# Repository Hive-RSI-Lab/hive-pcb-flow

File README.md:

# hive-pcb-flow

The pcb-flow module: KiCad hardware design for the Hive, in the Hive org like the other modules. It began as ihsan-sa/pcb-flow's Claude Code skill and is its own now ([where it came from](docs/upstream.md)).

An agent designs a PCB from a written brief: research, architecture, parts, schematic, placement, routing, then the checks (ERC, DRC, the verify suite, JLCPCB DFM on the exported Gerbers), ending in a fab package. The person signs off between stages. Ordering and paying are always the person's.

- [`docs/README.md`](docs/README.md): how an agent uses it in the Hive; [`docs/playbook.md`](docs/playbook.md): the phases, gates and fix loop
- `agents/`: the role prompts the playbook spawns; `scripts/`: the checks and tools; `reference/`: their tables, recipes, checklists and knowledge records
- [`docs/tools.md`](docs/tools.md): every tool pcb-flow uses, with licences and how to install it
- `tests/`: unit tests for the scripts (`test_env_lookups.py`: the lookups for the Hive's shared tools folder), and `tests/workarounds/`, the probes
- `bin/pcb-flow`: runs the scripts in a Hive sandbox with the Hive's KiCad 10 and freerouting (`pcb-flow check` first)
- The first board made with it: [boards/hwde-led-test/](boards/hwde-led-test/)
- [docs/errata-corpus.md](docs/errata-corpus.md): public boards whose rev B fixed a rev A defect, and which of those defects pcb-flow's checks catch on rev A (`bin/pcb-flow errata_corpus fetch|run|table`)
- [docs/miss-taxonomy.md](docs/miss-taxonomy.md): the corpus misses grouped by the check that would see them, ranked by count times how much of a board the check judges
- [docs/research/](docs/research/README.md): current research turned into checks: `bin/pcb-flow papers` scans the topics in `reference/research/watch.yaml`, reads legitimate open copies (the rest go on [the person's list](docs/research/paywalled.md)), and gives each claim pcb-flow's own verdict, with the test that reached it; only reproduced claims become [guidelines](docs/research/guidelines.md)
- [docs/route-quality.md](docs/route-quality.md): a layout judged as good, not only legal: `route_quality` scores each net class against its shortest 45-degree routes, `route_improve` re-routes the worst nets in rounds and stops when a round stops gaining
- `bin/pcb-flow part_repair`: move, rotate or re-pad parts on a routed board (place_edit's `swap_fp` puts a fixed library footprint in, `renumber` gives pads new numbers): it rips the copper the change spoils in a window round each part, makes the change, routes every net back to as few islands as it had, and keeps the result only if no net has more islands, DRC is no worse and no violation is new near the repair; it writes the op files that replay it (rip, place, route) and a REPORT.md

## Tools and credits

pcb-flow stands on other people's open-source tools: [KiCad](https://www.kicad.org/) for everything board-shaped, [KiCadRoutingTools](https://github.com/drandyhaas/KiCadRoutingTools) by Andy Haas (MIT) for escape and critical routing, [Freerouting](https://github.com/freerouting/freerouting) for bulk routing, [easyeda2kicad](https://github.com/uPesy/easyeda2kicad.py) for LCSC parts, and ngspice, Xyce, openEMS, Palace, gmsh, FastHenry2 and FasterCap (from the IIC-OSIC-TOOLS image) for simulation. [docs/tools.md](docs/tools.md) lists every tool with its version, licence, what it is for and how a fresh Hive gets it; `bin/pcb-flow check` shows what a machine has. [NOTICE](NOTICE) says what the MIT licence does not cover.

## Test and score

- **Test**, `bin/pcb-flow test`, run on every change: upstream's unit tests
  for the skill's scripts (in `tests/`, from ihsan-sa/pcb-flow, about 2,400 of
  them) and the workaround probes. It leaves out tests marked `smoke` (a
  live KiCad run) or `net` (the internet), and points `HWDE_BOARDS_ROOT` at
  an empty dir, so tests that want a real board skip. Upstream tests that
  fail here for a cause a brief already owns are expected failures, listed
  with that brief in `tests/conftest.py`; one that starts passing shows as
  XPASS, and its line comes out. `tests/test_workarounds.py` runs every
  probe in `tests/workarounds/` and fails when
  [docs/workarounds.md](docs/workarounds.md) doesn't match them: a cause
  that stands with no row, or a row whose cause is fixed. It also leaves
  out the tests listed as `slow` in `tests/conftest.py` (`SLOW`: the live
  toolchain, whole fixture boards through bench or the gates, intake of a
  whole project); `bin/pcb-flow test-slow` runs those, so run it too on a change
  to the checks, bench, intake or `check_env`. `bin/pcb-flow test-em` runs the long
  full-wave solves test-slow leaves out (`EM` in `tests/conftest.py`, 80 min
  against test-slow's 17 on a machine at load 45), so run it on a change to `scripts/lib/em*`
  or `scripts/lib/solvers.py`. A test past its limit (15 min, 45 in `em`) fails
  by name. `bin/pcb-flow test-smoke` runs the
  `smoke` tests, whole flows on a live KiCad; CI runs them on every PR and
  daily (`.github/workflows/smoke.yml`), and a failed daily run opens an issue. The test keeps its scratch
  files on `/dev/shm` when it has room and nothing in it fsyncs
  (`HWDE_NO_FSYNC`), because on a loaded disk the suite's file writes, not
  its CPU, set its time; it prints its time and its slowest 15 tests at
  the end. A few minutes; pytest arguments pass through
  (`bin/pcb-flow test tests/test_fab.py -x`).
- **Boards**, `bin/pcb-flow check-all`, not the per-change test: copies every
  board under `boards/` to a scratch dir and re-runs its gate steps there
  through `bin/pcb-flow`: `erc`, `drc_routed`, `verify`, `fab` (gerbers, drill,
  BOM and CPL from `fab_export` and `bom_cpl`) and `dfm`. A board runs each
  gate its `state.json` records as passed, and `fab` once it has a package
  in `fab/`. Any step that fails fails it, and it runs the probes too. Its
  time grows with every board, so run it on a change to the gates, the
  shims in `bin/pcb-flow` or a board, and before a release. Both need
  `/hive/tools`'s KiCad and the Hive's uv; on a fresh HOME they build the
  venv first. Inside a Hive turn both, and the scripts that run a whole
  board, the router or a sim (`route_auto`, `route_critical`,
  `place_anneal`, `gate`, `verify_all`, `bench`, `render`, `sim_run`,
  `sim_solve`, `fab_export`), run under `hive agent heavy`: they wait (at most 10
  minutes) while the machine is strained and other turns run one. A command
  already inside one (check-all's gates, a test that runs `bin/pcb-flow`), or a
  Hive without that op yet, runs bare (`tests/test_heavy.py`).
- **Score**, `bin/pcb-flow score`, higher is better: what this checkout's
  gates get wrong on boards held fixed. The hi-fi receiver's lite-main, core and ultra-front,
  pinned in `pinned/` at one hifi-receiver-2 commit, and hwde-led-test go
  through erc, drc_routed, verify and dfm with `bin/pcb-flow`'s shims off. Each board's
  ledger (`pinned/known/<board>.json`) judges its findings: one held real
  is the board's defect and costs nothing; one held false, one not judged
  yet, a known real one no gate reports any more, and each board-local
  script that stands in for pcb-flow is a charge, and the score is minus the
  charges. A fix in pcb-flow that clears a false finding on those boards raises
  it with nothing written by hand; a sharper check's new real findings go
  into the ledger in the same change. A pinned board changes only through `bin/pcb-flow pin`. The whole
  definition is [docs/score.md](docs/score.md). About ten minutes or more,
  under `hive agent heavy`. A looser check finds less, so the score also
  runs pcb-flow's planted faults (`bin/strength.py`: the gate criteria, every
  verify check's mutant in `tests/golden/`, dfm at JLC's floors), and each
  one a check lets through charges 100.
- **Frozen**, `bin/pcb-flow frozen test` (or `test-slow`, `check-all`,
  `score`, or `-- CMD`): runs the command on a copy of the checkout taken
  now (HEAD plus uncommitted edits, deletions and untracked files, not
  ignored ones) and removes the copy after. A run that waits in a heavy
  queue, or an edit made while it runs, then can't change what it judges;
  paths into the checkout point into the copy, and it exits with the
  command's status ([bin/frozen.py](bin/frozen.py)). Budget more time:
  the full `test` took 1177 s frozen against 997 s plain (about a fifth
  more), so raise the `heavy timeout` to match.

MIT, like upstream; see NOTICE for what that doesn't cover.

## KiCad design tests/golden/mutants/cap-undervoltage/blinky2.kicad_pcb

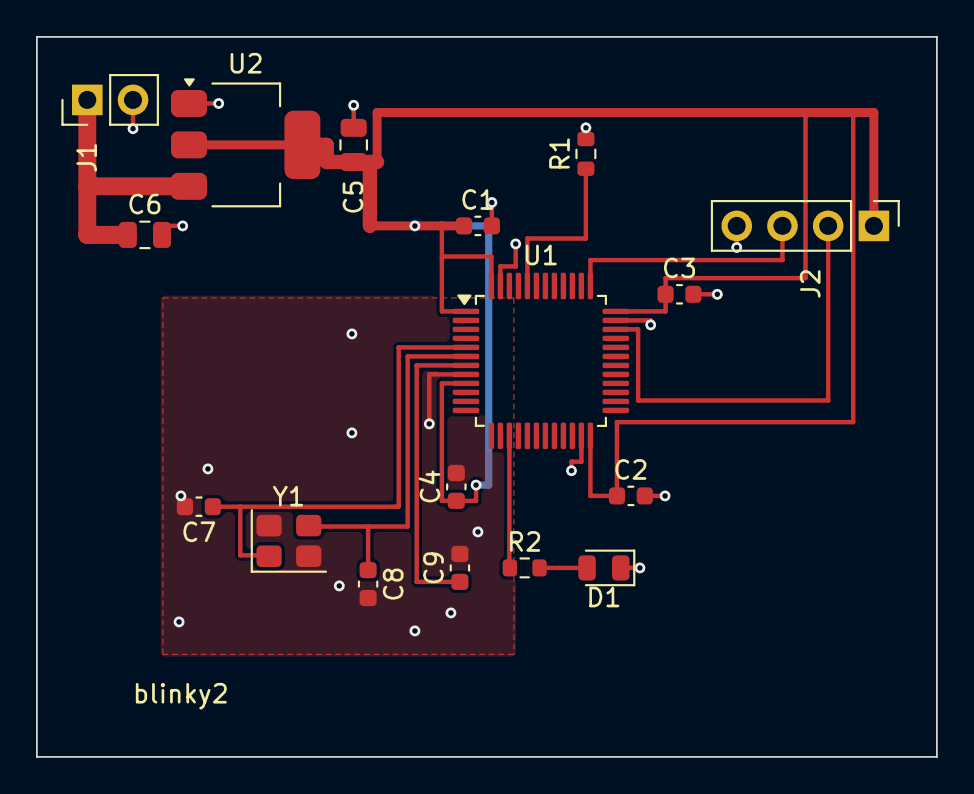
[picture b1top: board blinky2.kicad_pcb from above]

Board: 2 copper layers, 50.0 x 40.0 mm, 17 parts (0 on the bottom side), 11 nets.

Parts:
C1, C2, C3, C4, C9: 100nF; C_0603_1608Metric
C5, C6: 10uF; C_0805_2012Metric
C7, C8: 22pF; C_0603_1608Metric
D1: LED_red; LED_0805_2012Metric
J1: PWR_5V; PinHeader_1x02_P2.54mm_Vertical
J2: SWD; PinHeader_1x04_P2.54mm_Vertical
R1: 10k; R_0603_1608Metric
R2: 470; R_0603_1608Metric
U1: STM32F103C8T6; LQFP-48_7x7mm_P0.5mm
U2: AMS1117-3.3; SOT-223-3_TabPin2
Y1: 8MHz; Crystal_SMD_3225-4Pin_3.2x2.5mm

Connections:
+3V3: C1.1, C2.1, C3.1, C4.1, C5.1, J2.1, U1.1, U1.9, U1.24, U1.36, U1.48, U2.2
+5V: C6.1, J1.1, U2.3
/BOOT0: R1.1, U1.44
/LED: R2.1, U1.15
/LED_A: D1.2, R2.2
/NRST: C9.1, U1.7
/OSC_IN: C7.1, U1.5, Y1.1
/OSC_OUT: C8.1, U1.6, Y1.3
/SWCLK: J2.3, U1.37
/SWDIO: J2.2, U1.34
GND: C1.2, C2.2, C3.2, C4.2, C5.2, C6.2, C7.2, C8.2, C9.2, D1.1, J1.2, J2.4, R1.2, U1.8, U1.23, U1.35, U1.47, U2.1, Y1.2, Y1.4

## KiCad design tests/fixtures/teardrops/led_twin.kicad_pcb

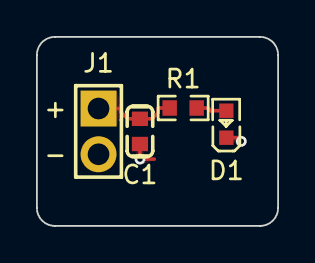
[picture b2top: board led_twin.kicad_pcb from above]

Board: 2 copper layers, 13.4 x 10.5 mm, 4 parts (0 on the bottom side), 3 nets.

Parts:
C1: 4.7uF; C0603
D1: KT-0603G; LED0603-RD
J1: PZ254V-11-02P; HDR-TH_2P-P2.54-V-M
R1: 470R; R0603

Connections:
+5V: C1.1, J1.1, R1.1
/LED_A: D1.2, R1.2
GND: C1.2, D1.1, J1.2
